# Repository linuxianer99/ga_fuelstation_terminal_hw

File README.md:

# GA_FuelStation_Terminal_HW

## Name
This is the hardware repository for GA GA_FuelStation_Terminal

## Description
KICAD Project for an RFID Terminal based on ESP32-S3

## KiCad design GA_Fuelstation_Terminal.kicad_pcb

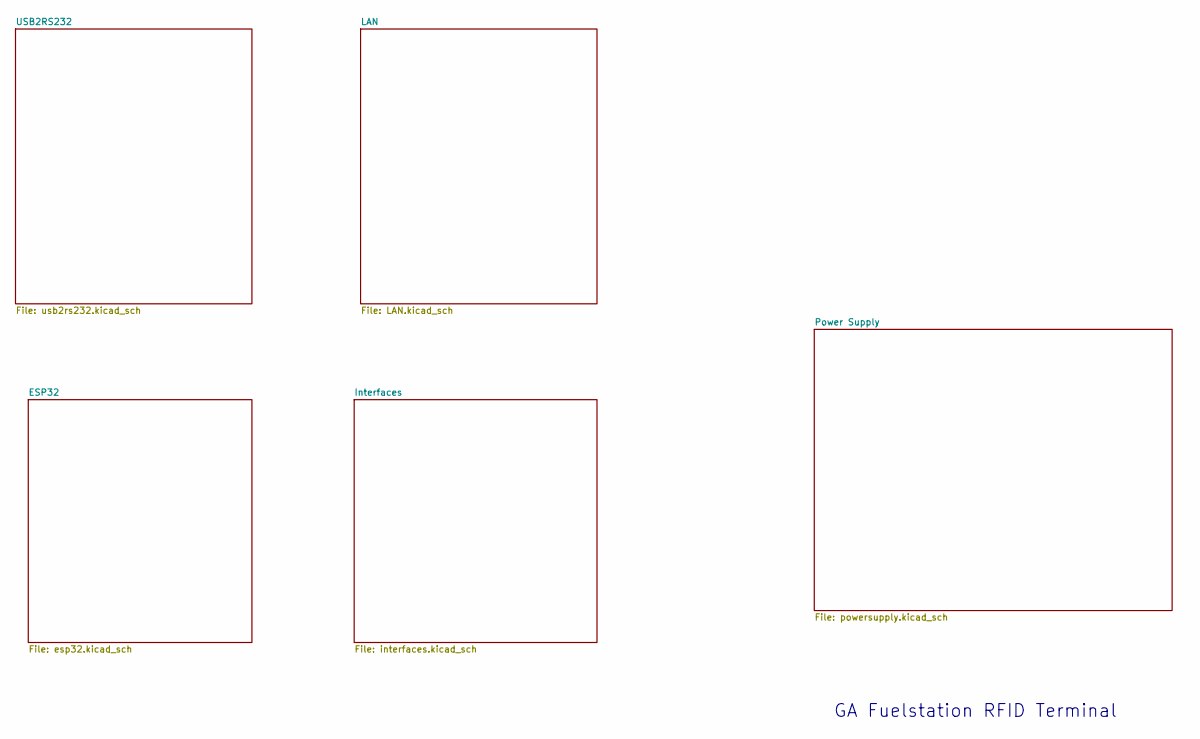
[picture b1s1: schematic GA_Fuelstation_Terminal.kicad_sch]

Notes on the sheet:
GA Fuelstation RFID Terminal

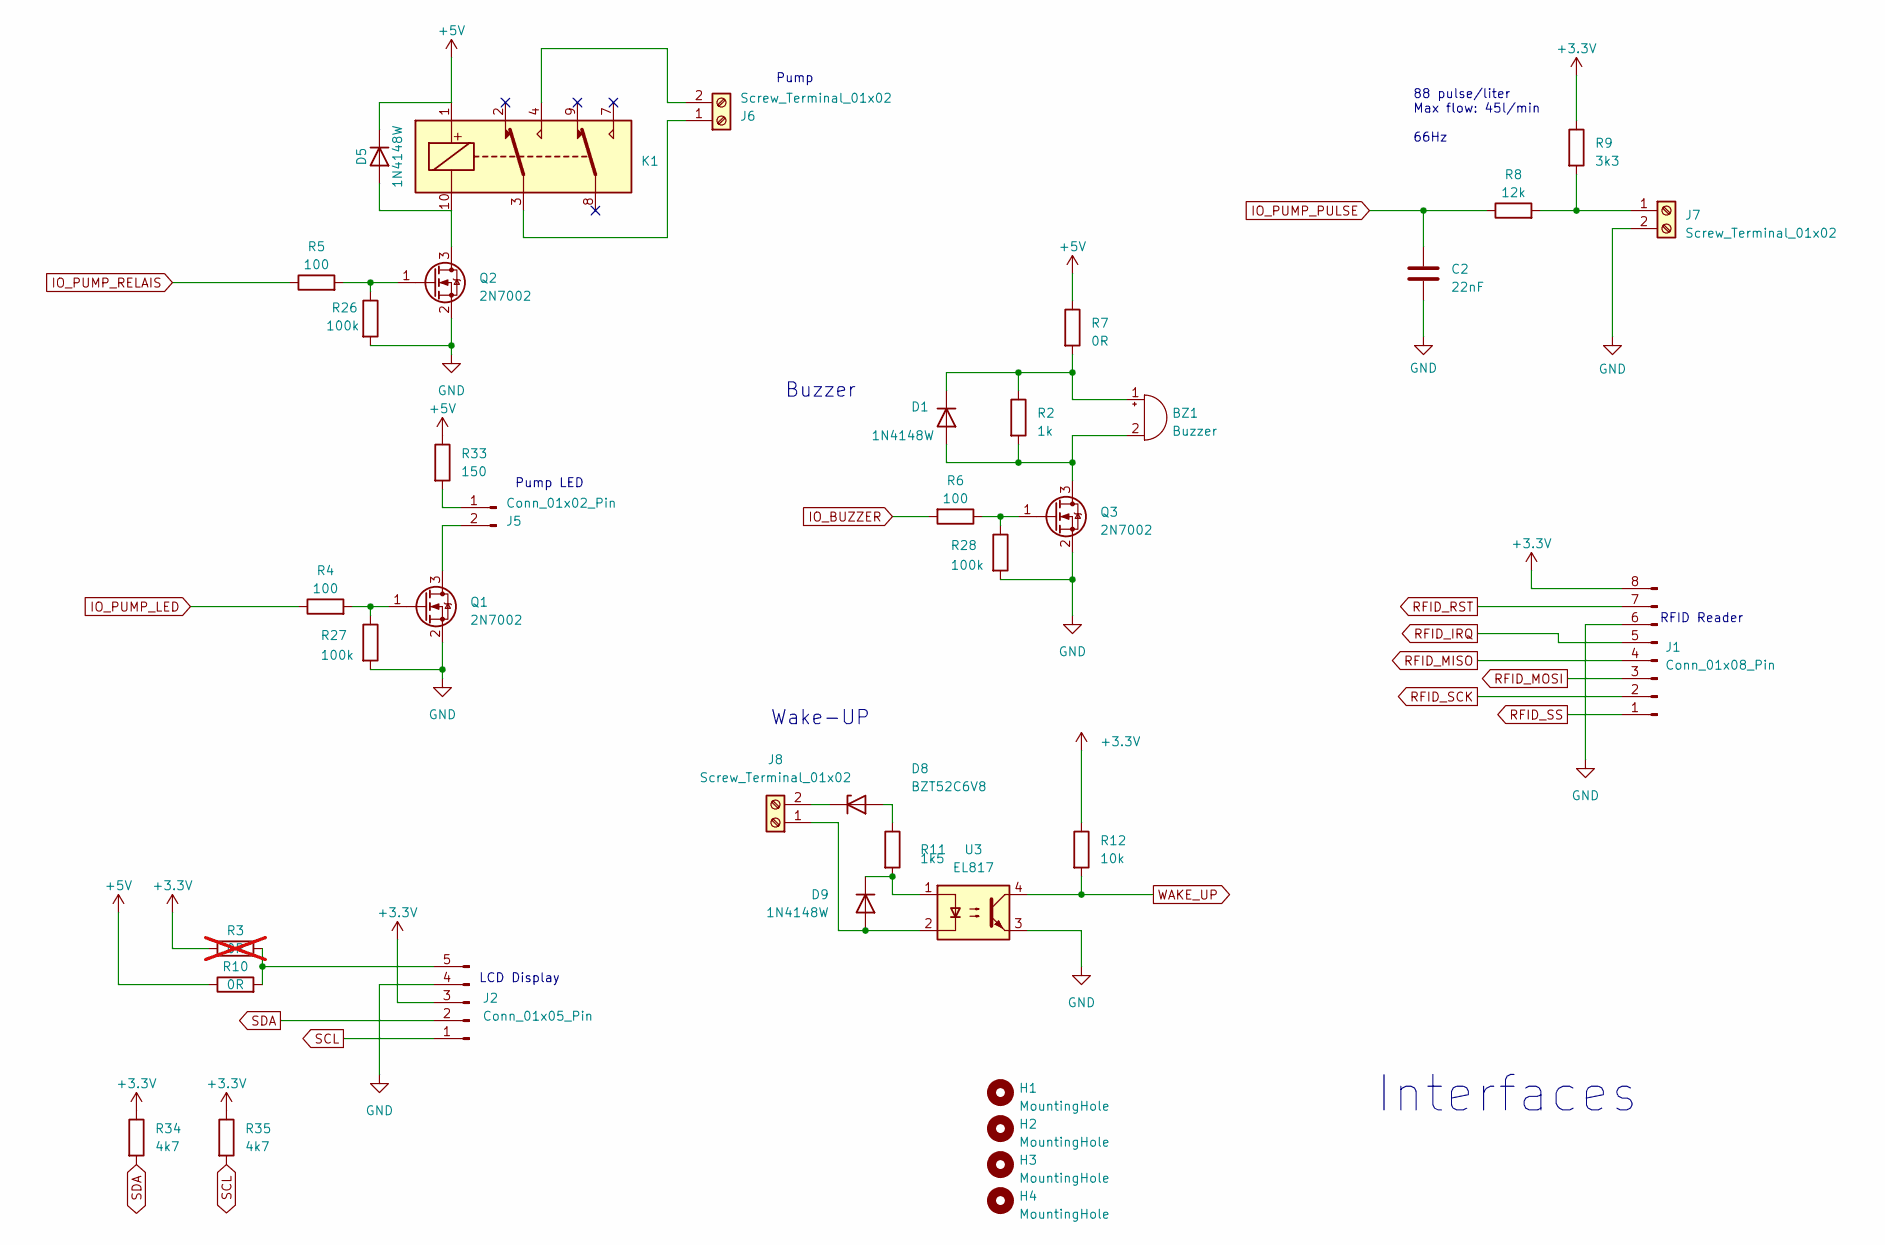
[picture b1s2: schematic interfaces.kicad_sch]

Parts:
BZ1: Buzzer; 8530-SMD; LCSC C94599
C2: 22nF; C_0603_1608Metric_Pad1.08x0.95mm_HandSolder; LCSC C21122
D1, D5, D9: 1N4148W; D_SOD-123; LCSC C81598
D8: BZT52C6V8; D_SOD-123; LCSC C173404
H1, H2, H3, H4: MountingHole; MountingHole_3.2mm_M3
J1: Conn_01x08_Pin; JST_XH_B8B-XH-AM_1x08_P2.50mm_Vertical; LCSC C161875
J2: Conn_01x05_Pin; JST_XH_B5B-XH-AM_1x05_P2.50mm_Vertical; LCSC C161872
J5: Conn_01x02_Pin; JST_XH_B2B-XH-AM_1x02_P2.50mm_Vertical; LCSC C161869
J6, J7, J8: Screw_Terminal_01x02; PhoenixContact_MSTBA_2,5_2-G-5,08_1x02_P5.08mm_Horizontal; LCSC C90074
K1: TQ2SA; LCSC C22686
Q1, Q2, Q3: 2N7002; SOT-23; LCSC C8545
R2: 1k; R_0805_2012Metric_Pad1.20x1.40mm_HandSolder; LCSC C17513
R3: 0R; R_0805_2012Metric_Pad1.20x1.40mm_HandSolder; LCSC C17477; not fitted
R4, R5, R6: 100; R_0805_2012Metric_Pad1.20x1.40mm_HandSolder; LCSC C17408
R7: 0R; R_0805_2012Metric_Pad1.20x1.40mm_HandSolder
R8: 12k; R_0805_2012Metric_Pad1.20x1.40mm_HandSolder; LCSC C17444
R9: 3k3; R_0805_2012Metric_Pad1.20x1.40mm_HandSolder; LCSC C26010
R10: 0R; R_0805_2012Metric_Pad1.20x1.40mm_HandSolder; LCSC C17477
R11: 1k5; R_0805_2012Metric_Pad1.20x1.40mm_HandSolder; LCSC C4310
R12: 10k; R_0603_1608Metric_Pad0.98x0.95mm_HandSolder; LCSC C25804
R26, R27, R28: 100k; R_0402_1005Metric_Pad0.72x0.64mm_HandSolder; LCSC C25741
R33: 150; R_0805_2012Metric_Pad1.20x1.40mm_HandSolder; LCSC C17471
R34, R35: 4k7; R_0805_2012Metric_Pad1.20x1.40mm_HandSolder; LCSC C17673
U3: EL817; SMDIP-4_W9.53mm; LCSC C63268

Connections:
+3.3V: J1.8, J2.3, R3.1, R9.1, R12.1, R34.1, R35.1; also elsewhere on the board
+5V: D5.1 (K), K1.1, R7.1, R10.1, R33.1; also elsewhere on the board
GND: C2.2, J1.6, J2.4, J7.2, Q1.2 (S), Q2.2 (S), Q3.2 (S), R26.2, R27.2, R28.2, U3.3; also elsewhere on the board
IO_BUZZER: R6.2; also elsewhere on the board
IO_PUMP_LED: R4.1; also elsewhere on the board
IO_PUMP_PULSE: C2.1, R8.1; also elsewhere on the board
IO_PUMP_RELAIS: R5.1; also elsewhere on the board
unnamed: BZ1.2 (+), D1.2 (A), Q3.3 (D), R2.2
unnamed: BZ1.1 (-), D1.1 (K), R2.1, R7.2
unnamed: D5.2 (A), K1.10, Q2.3 (D)
unnamed: D8.2 (A), R11.1
unnamed: D8.1 (K), J8.2
unnamed: D9.2 (A), J8.1, U3.2
unnamed: D9.1 (K), R11.2, U3.1
unnamed: J2.5, R3.2, R10.2
unnamed: J5.1, R33.2
unnamed: J5.2, Q1.3 (D)
unnamed: J6.1, K1.3
unnamed: J6.2, K1.4
unnamed: J7.1, R8.2, R9.2
unnamed: Q1.1 (G), R4.2, R27.1
unnamed: Q2.1 (G), R5.2, R26.1
unnamed: Q3.1 (G), R6.1, R28.1
RFID_IRQ: J1.5; also elsewhere on the board
RFID_MISO: J1.4; also elsewhere on the board
RFID_MOSI: J1.3; also elsewhere on the board
RFID_RST: J1.7; also elsewhere on the board
RFID_SCK: J1.2; also elsewhere on the board
RFID_SS: J1.1; also elsewhere on the board
SCL: J2.1, R35.2; also elsewhere on the board
SDA: J2.2, R34.2; also elsewhere on the board
WAKE_UP: R12.2, U3.4; also elsewhere on the board

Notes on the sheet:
Buzzer
RFID Reader
Pump
88 pulse/liter Max flow: 45l/min 66Hz
Wake-UP
LCD Display
Pump LED
Interfaces

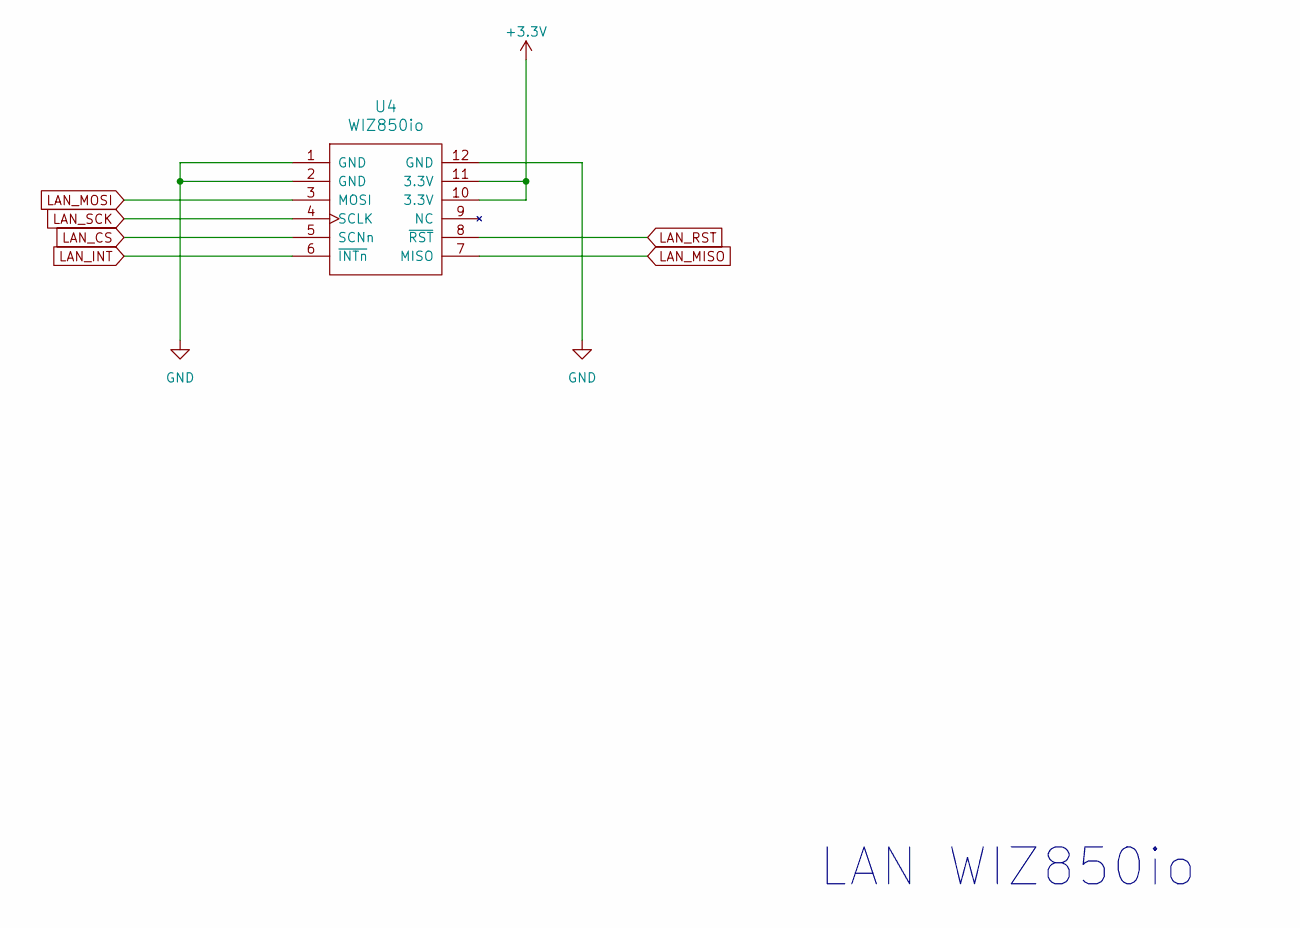
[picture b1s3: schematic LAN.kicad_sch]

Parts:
U4: WIZ850io

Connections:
+3.3V: U4.10 (3.3V), U4.11 (3.3V); also elsewhere on the board
GND: U4.1 (GND), U4.2 (GND), U4.12 (GND); also elsewhere on the board
LAN_CS: U4.5 (SCNn); also elsewhere on the board
LAN_INT: U4.6 (~INTn); also elsewhere on the board
LAN_MISO: U4.7 (MISO); also elsewhere on the board
LAN_MOSI: U4.3 (MOSI); also elsewhere on the board
LAN_RST: U4.8 (~RST); also elsewhere on the board
LAN_SCK: U4.4 (SCLK); also elsewhere on the board

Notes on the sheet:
LAN WIZ850io

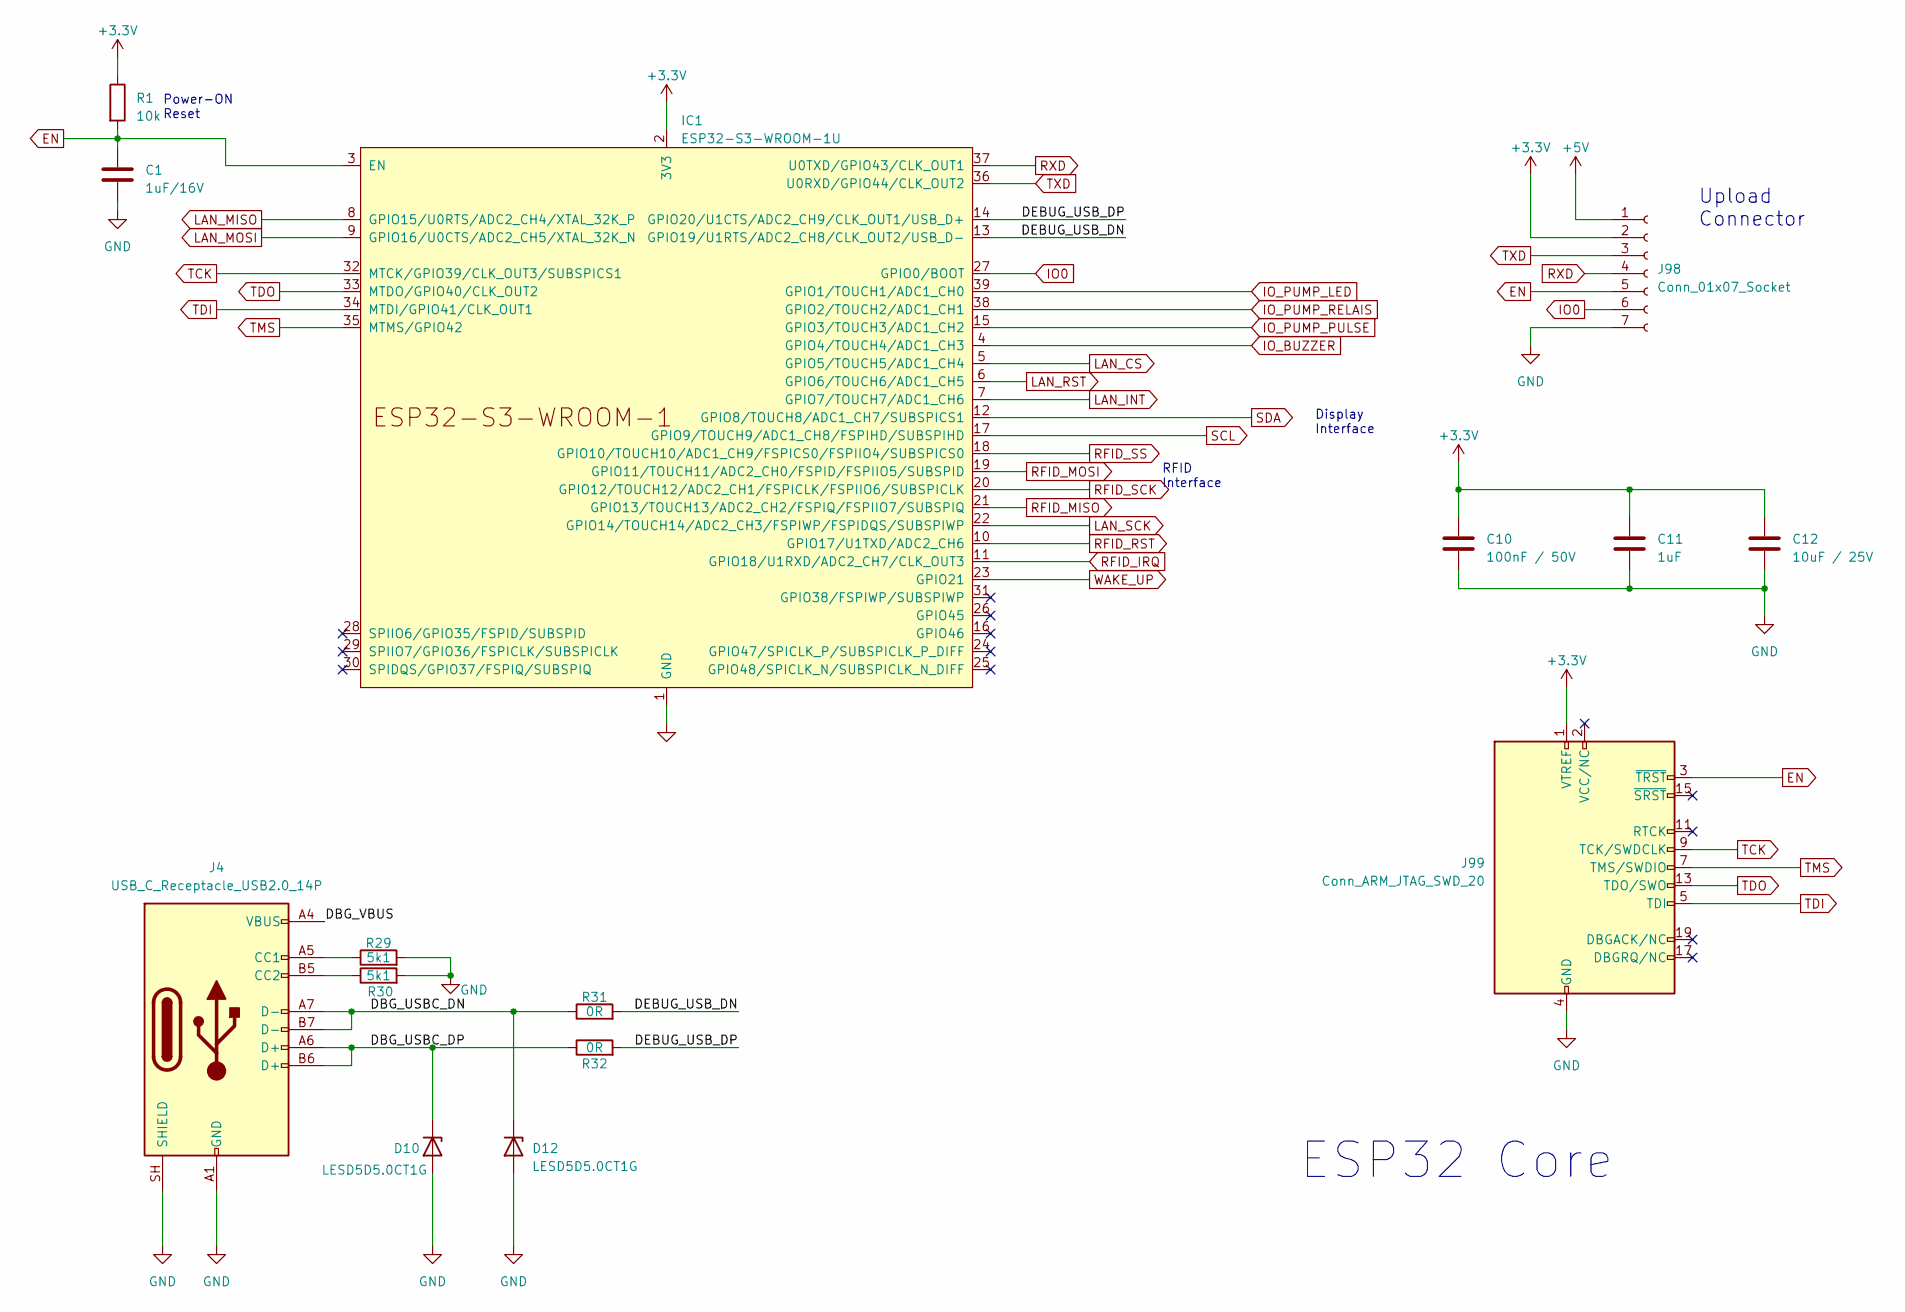
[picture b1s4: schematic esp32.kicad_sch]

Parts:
C1: 1uF/16V; C_0603_1608Metric_Pad1.08x0.95mm_HandSolder; LCSC C15849
C10: 100nF / 50V; C_0402_1005Metric_Pad0.74x0.62mm_HandSolder; LCSC C307331
C11: 1uF; C_0805_2012Metric_Pad1.18x1.45mm_HandSolder; LCSC C28323
C12: 10uF / 25V; C_1206_3216Metric_Pad1.33x1.80mm_HandSolder; LCSC C13585
D10, D12: LESD5D5.0CT1G; D_SOD-523; LCSC C41399463
IC1: ESP32-S3-WROOM-1U; LCSC C3013946
J4: USB_C_Receptacle_USB2.0_14P; USB_C_Receptacle_HRO_TYPE-C-31-M-12; LCSC C165948
J98: Conn_01x07_Socket; JST_XH_B7B-XH-AM_1x07_P2.50mm_Vertical; LCSC C161874
J99: Conn_ARM_JTAG_SWD_20; IDC-Header_2x10_P2.54mm_Vertical; LCSC C3405
R1: 10k; R_0603_1608Metric_Pad0.98x0.95mm_HandSolder; LCSC C25804
R29, R30: 5k1; R_0603_1608Metric_Pad0.98x0.95mm_HandSolder; LCSC C23186
R31, R32: 0R; R_0402_1005Metric; LCSC C17168

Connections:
+3.3V: C10.1, C11.1, C12.1, IC1.2 (3V3), J98.2, J99.1 (VTREF), R1.1; also elsewhere on the board
+5V: J98.1; also elsewhere on the board
/ESP32/DBG_USBC_DN: D12.1 (K), J4.A7 (D-), J4.B7 (D-), R31.1
/ESP32/DBG_USBC_DP: D10.1 (K), J4.A6 (D+), J4.B6 (D+), R32.1
/ESP32/DBG_VBUS: J4.A4 (VBUS), J4.A9 (VBUS), J4.B4 (VBUS), J4.B9 (VBUS)
/ESP32/DEBUG_USB_DN: IC1.13 (GPIO19/U1RTS/ADC2_CH8/CLK_OUT2/USB_D-), R31.2
/ESP32/DEBUG_USB_DP: IC1.14 (GPIO20/U1CTS/ADC2_CH9/CLK_OUT1/USB_D+), R32.2
EN: C1.1, IC1.3 (EN), J98.5, J99.3 (~TRST), R1.2; also elsewhere on the board
GND: C1.2, C10.2, C11.2, C12.2, D10.2 (A), D12.2 (A), IC1.1 (GND), IC1.40 (GND), IC1.41 (GND), J4.A1 (GND), J4.A12 (GND), J4.B1 (GND), J4.B12 (GND), J4.SH (SHIELD), J98.7, J99.4 (GND), J99.6 (GND), J99.8 (GND), J99.10 (GND), J99.12 (GND), J99.14 (GND), J99.16 (GND), J99.18 (GND), J99.20 (GND), R29.2, R30.2; also elsewhere on the board
IO0: IC1.27 (GPIO0/BOOT), J98.6; also elsewhere on the board
IO_BUZZER: IC1.4 (GPIO4/TOUCH4/ADC1_CH3); also elsewhere on the board
IO_PUMP_LED: IC1.39 (GPIO1/TOUCH1/ADC1_CH0); also elsewhere on the board
IO_PUMP_PULSE: IC1.15 (GPIO3/TOUCH3/ADC1_CH2); also elsewhere on the board
IO_PUMP_RELAIS: IC1.38 (GPIO2/TOUCH2/ADC1_CH1); also elsewhere on the board
LAN_CS: IC1.5 (GPIO5/TOUCH5/ADC1_CH4); also elsewhere on the board
LAN_INT: IC1.7 (GPIO7/TOUCH7/ADC1_CH6); also elsewhere on the board
LAN_MISO: IC1.8 (GPIO15/U0RTS/ADC2_CH4/XTAL_32K_P); also elsewhere on the board
LAN_MOSI: IC1.9 (GPIO16/U0CTS/ADC2_CH5/XTAL_32K_N); also elsewhere on the board
LAN_RST: IC1.6 (GPIO6/TOUCH6/ADC1_CH5); also elsewhere on the board
LAN_SCK: IC1.22 (GPIO14/TOUCH14/ADC2_CH3/FSPIWP/FSPIDQS/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); also elsewhere on the board
unnamed: J4.A5 (CC1), R29.1
unnamed: J4.B5 (CC2), R30.1
RFID_IRQ: IC1.11 (GPIO18/U1RXD/ADC2_CH7/CLK_OUT3); also elsewhere on the board
RFID_MISO: IC1.21 (GPIO13/TOUCH13/ADC2_CH2/FSPIQ/FSPIIO7/S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); also elsewhere on the board
RFID_MOSI: IC1.19 (GPIO11/TOUCH11/ADC2_CH0/FSPID/FSPIIO5/S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); also elsewhere on the board
RFID_RST: IC1.10 (GPIO17/U1TXD/ADC2_CH6); also elsewhere on the board
RFID_SCK: IC1.20 (GPIO12/TOUCH12/ADC2_CH1/FSPICLK/FSPIIO6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); also elsewhere on the board
RFID_SS: IC1.18 (GPIO10/TOUCH10/ADC1_CH9/FSPICS0/FSPIIO4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); also elsewhere on the board
RXD: IC1.37 (U0TXD/GPIO43/CLK_OUT1), J98.4; also elsewhere on the board
SCL: IC1.17 (GPIO9/TOUCH9/ADC1_CH8/FSPIHD/SUBSPIHD); also elsewhere on the board
SDA: IC1.12 (GPIO8/TOUCH8/ADC1_CH7/SUBSPICS1); also elsewhere on the board
TCK: IC1.32 (MTCK/GPIO39/CLK_OUT3/SUBSPICS1), J99.9 (TCK/SWDCLK)
TDI: IC1.34 (MTDI/GPIO41/CLK_OUT1), J99.5 (TDI)
TDO: IC1.33 (MTDO/GPIO40/CLK_OUT2), J99.13 (TDO/SWO)
TMS: IC1.35 (MTMS/GPIO42), J99.7 (TMS/SWDIO)
TXD: IC1.36 (U0RXD/GPIO44/CLK_OUT2), J98.3; also elsewhere on the board
WAKE_UP: IC1.23 (GPIO21); also elsewhere on the board

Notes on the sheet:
Upload Connector
ESP32 Core
Display Interface
RFID Interface
Power-ON Reset

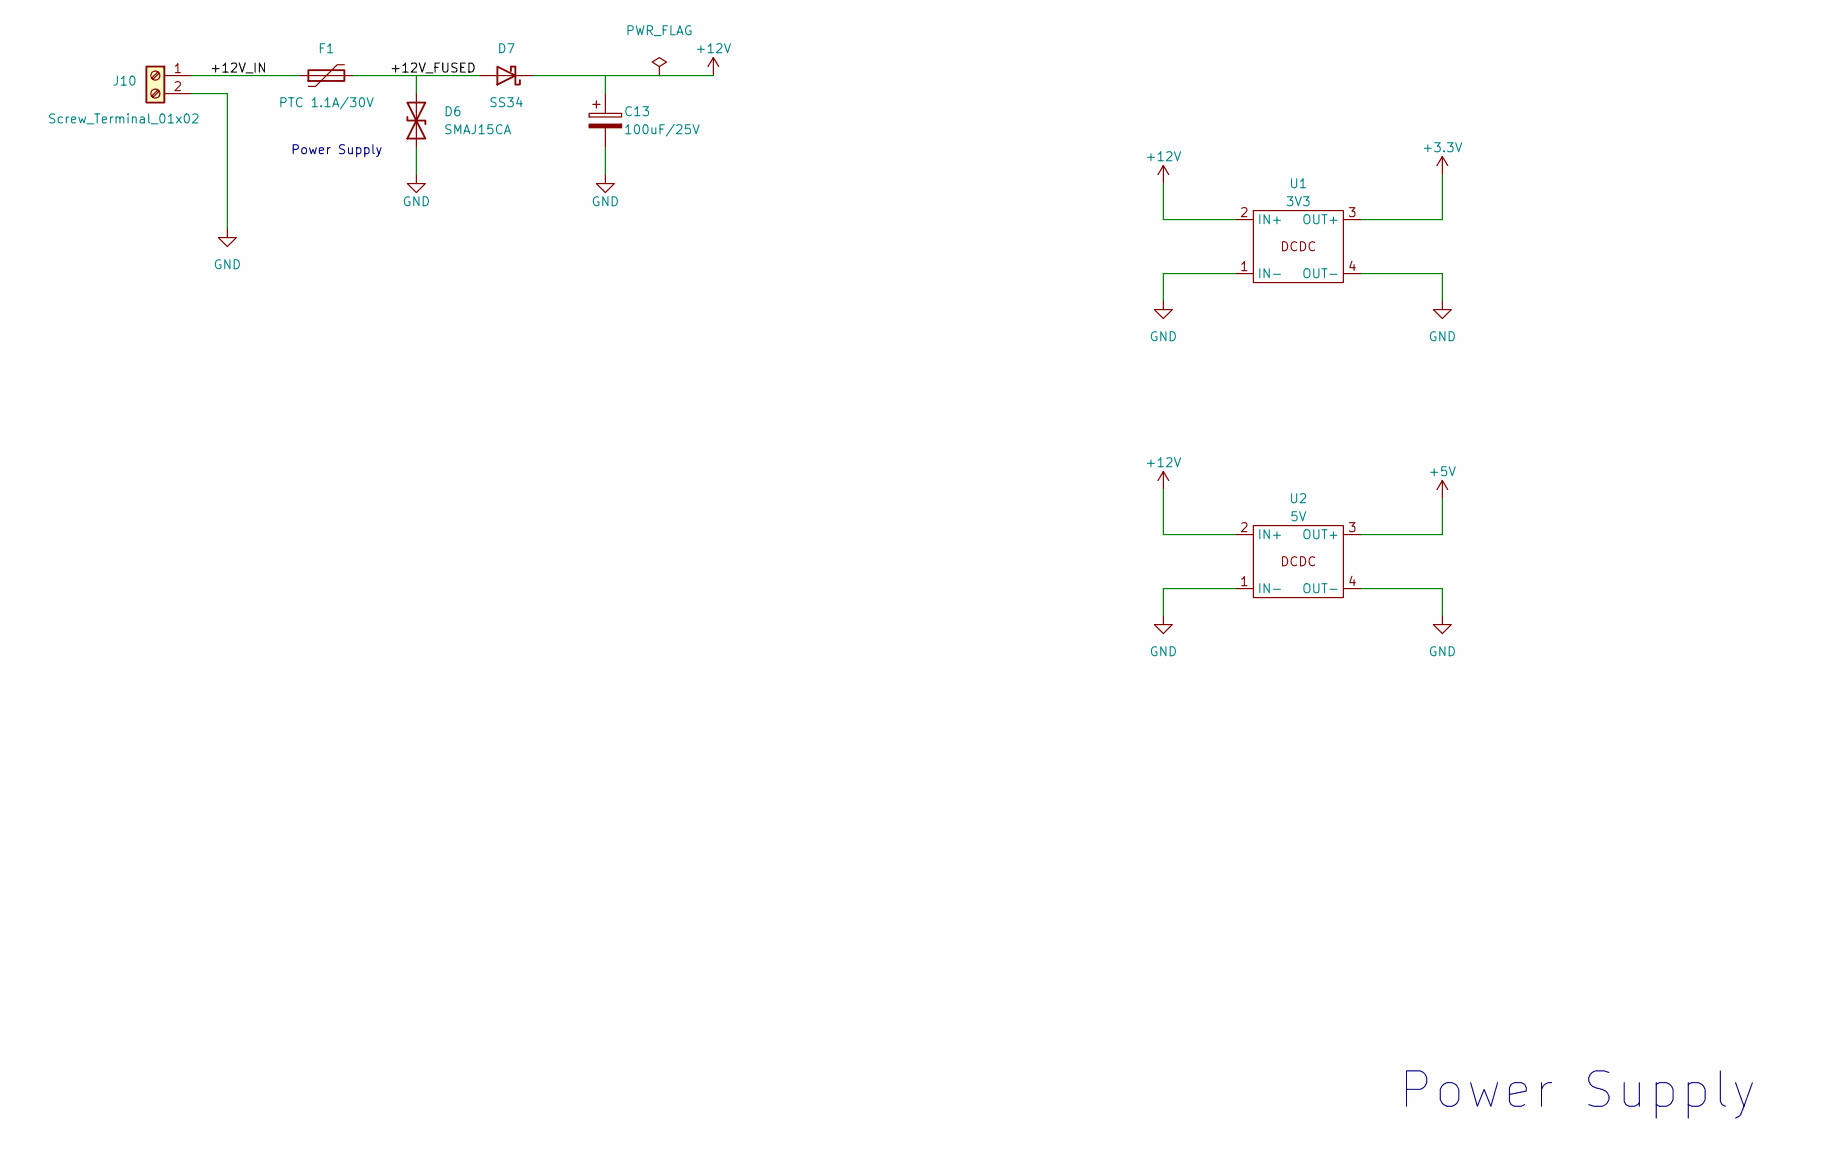
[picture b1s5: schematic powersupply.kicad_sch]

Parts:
C13: 100uF/25V; CP_Elec_6.3x7.7; LCSC C72477
D6: SMAJ15CA; D_SMA; LCSC C151939
D7: SS34; D_SMA; LCSC C8678
F1: PTC 1.1A/30V; Fuse_1812_4532Metric; LCSC C70119
J10: Screw_Terminal_01x02; PhoenixContact_MSTBA_2,5_2-G-5,08_1x02_P5.08mm_Horizontal; LCSC C90074
U1: 3V3; XLZMYQ
U2: 5V; XLZMYQ

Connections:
+3.3V: U1.3 (OUT+); also elsewhere on the board
+5V: U2.3 (OUT+); also elsewhere on the board
+12V: C13.1, D7.1 (K), U1.2 (IN+), U2.2 (IN+)
/Power Supply/+12V_FUSED: D6.2 (A2), D7.2 (A), F1.2
/Power Supply/+12V_IN: F1.1, J10.1
GND: C13.2, D6.1 (A1), J10.2, U1.1 (IN-), U1.4 (OUT-), U2.1 (IN-), U2.4 (OUT-); also elsewhere on the board

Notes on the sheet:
Power Supply

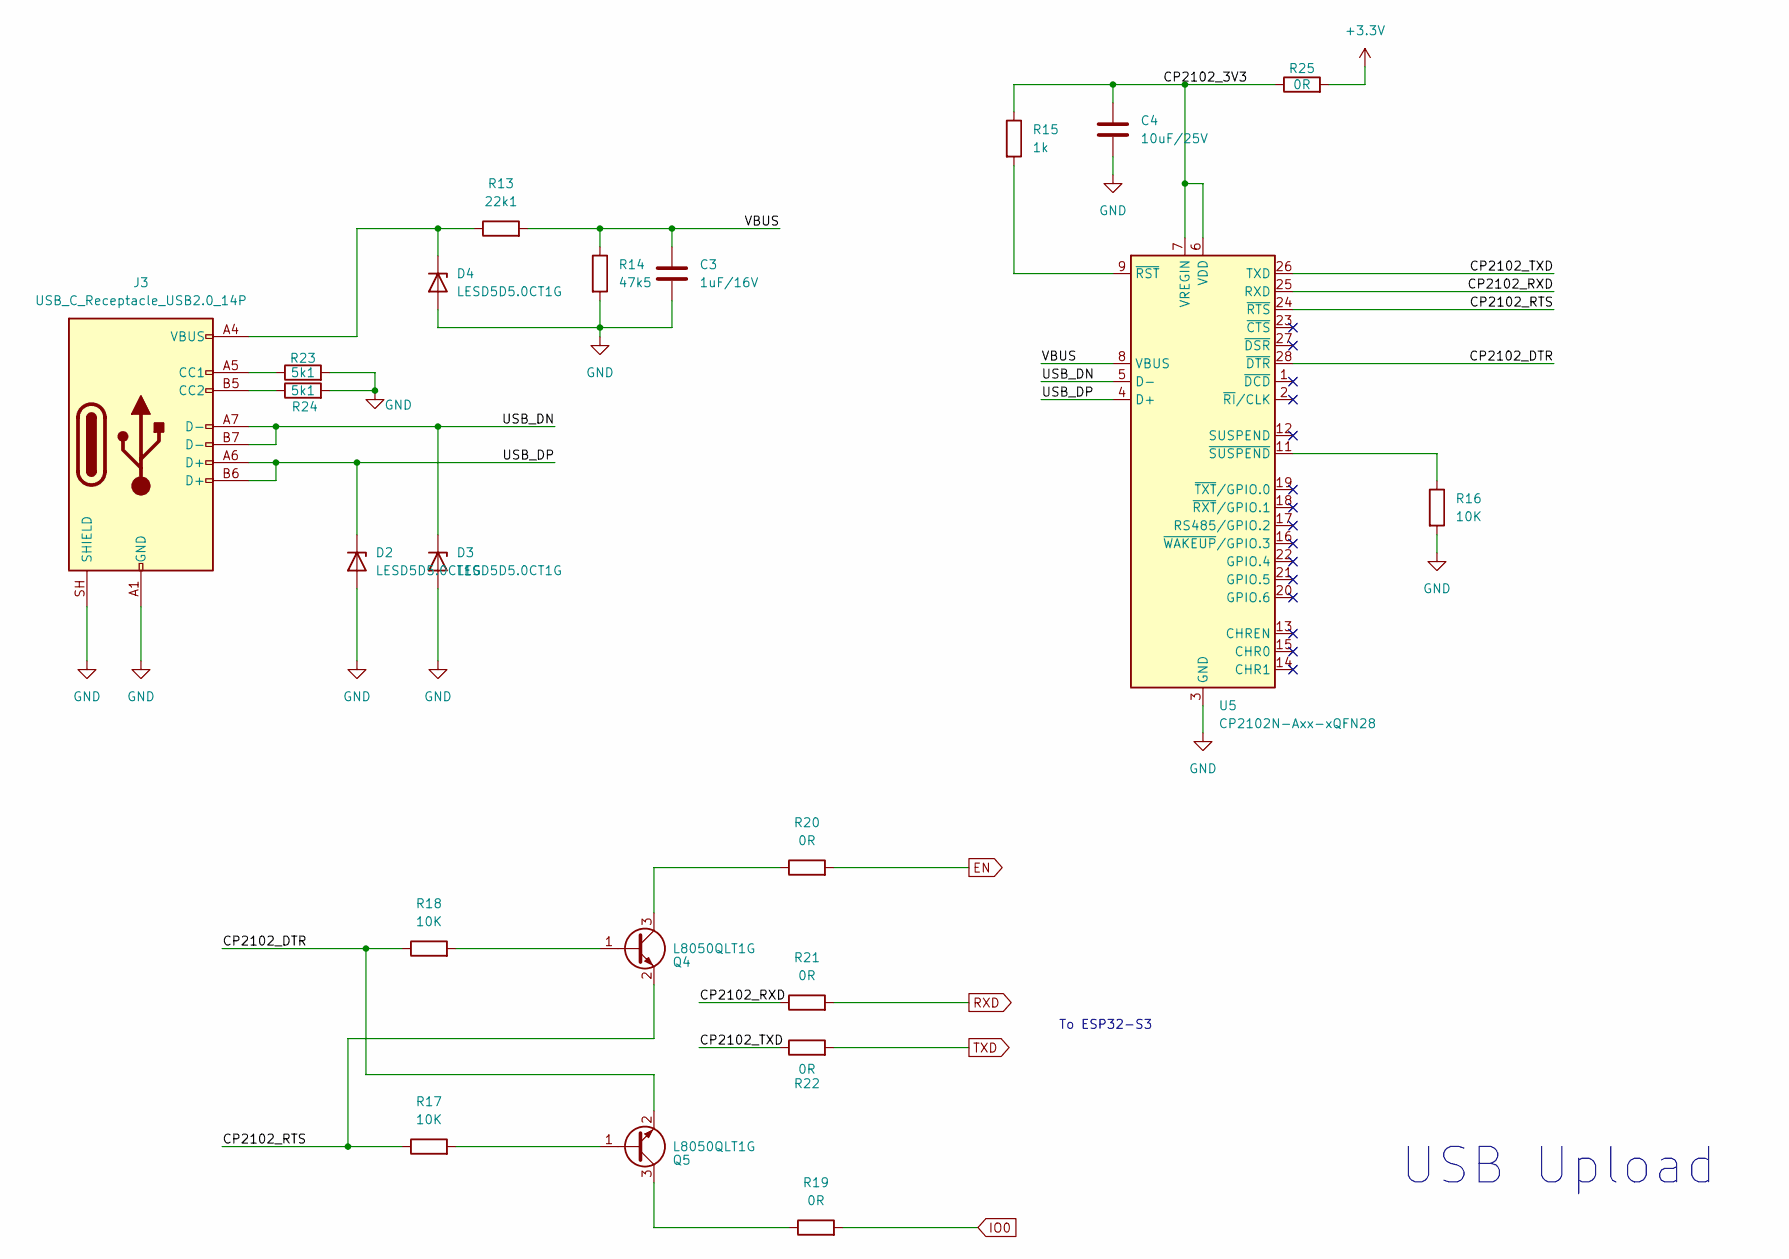
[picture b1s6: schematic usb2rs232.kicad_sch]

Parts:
C3: 1uF/16V; C_0603_1608Metric; LCSC C15849
C4: 10uF/25V; C_0603_1608Metric; LCSC C96446
D2, D3, D4: LESD5D5.0CT1G; D_SOD-523; LCSC C41399463
J3: USB_C_Receptacle_USB2.0_14P; USB_C_Receptacle_HRO_TYPE-C-31-M-12; LCSC C165948
Q4, Q5: L8050QLT1G; SOT-23; LCSC C49581
R13: 22k1; R_0402_1005Metric; LCSC C163478
R14: 47k5; R_0402_1005Metric; LCSC C324818
R15: 1k; R_0402_1005Metric; LCSC C11702
R16, R17, R18: 10K; R_0402_1005Metric; LCSC C25744
R19, R20, R21, R22: 0R; R_0402_1005Metric; LCSC C17168
R23, R24: 5k1; R_0603_1608Metric_Pad0.98x0.95mm_HandSolder; LCSC C23186
R25: 0R; R_0402_1005Metric_Pad0.72x0.64mm_HandSolder; LCSC C17168
U5: CP2102N-Axx-xQFN28; QFN-28-1EP_5x5mm_P0.5mm_EP3.35x3.35mm; LCSC C964632

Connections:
+3.3V: R25.2; also elsewhere on the board
/USB2RS232/CP2102_3V3: C4.1, R15.1, R25.1, U5.6 (VDD), U5.7 (VREGIN)
/USB2RS232/CP2102_DTR: Q5.2 (E), R18.1, U5.28 (~DTR)
/USB2RS232/CP2102_RTS: Q4.2 (E), R17.1, U5.24 (~RTS)
/USB2RS232/CP2102_RXD: R21.1, U5.25 (RXD)
/USB2RS232/CP2102_TXD: R22.1, U5.26 (TXD)
/USB2RS232/USB_DN: D3.1 (K), J3.A7 (D-), J3.B7 (D-), U5.5 (D-)
/USB2RS232/USB_DP: D2.1 (K), J3.A6 (D+), J3.B6 (D+), U5.4 (D+)
/USB2RS232/VBUS: C3.1, R13.2, R14.1, U5.8 (VBUS)
EN: R20.2; also elsewhere on the board
GND: C3.2, C4.2, D2.2 (A), D3.2 (A), D4.2 (A), J3.A1 (GND), J3.A12 (GND), J3.B1 (GND), J3.B12 (GND), J3.SH (SHIELD), R14.2, R16.2, R23.2, R24.2, U5.3 (GND), U5.29 (GND); also elsewhere on the board
IO0: R19.2; also elsewhere on the board
unnamed: D4.1 (K), J3.A4 (VBUS), J3.A9 (VBUS), J3.B4 (VBUS), J3.B9 (VBUS), R13.1
unnamed: J3.A5 (CC1), R23.1
unnamed: J3.B5 (CC2), R24.1
unnamed: Q4.1 (B), R18.2
unnamed: Q4.3 (C), R20.1
unnamed: Q5.1 (B), R17.2
unnamed: Q5.3 (C), R19.1
unnamed: R15.2, U5.9 (~RST)
unnamed: R16.1, U5.11 (~SUSPEND)
RXD: R21.2; also elsewhere on the board
TXD: R22.2; also elsewhere on the board

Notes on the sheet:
To ESP32-S3
USB Upload

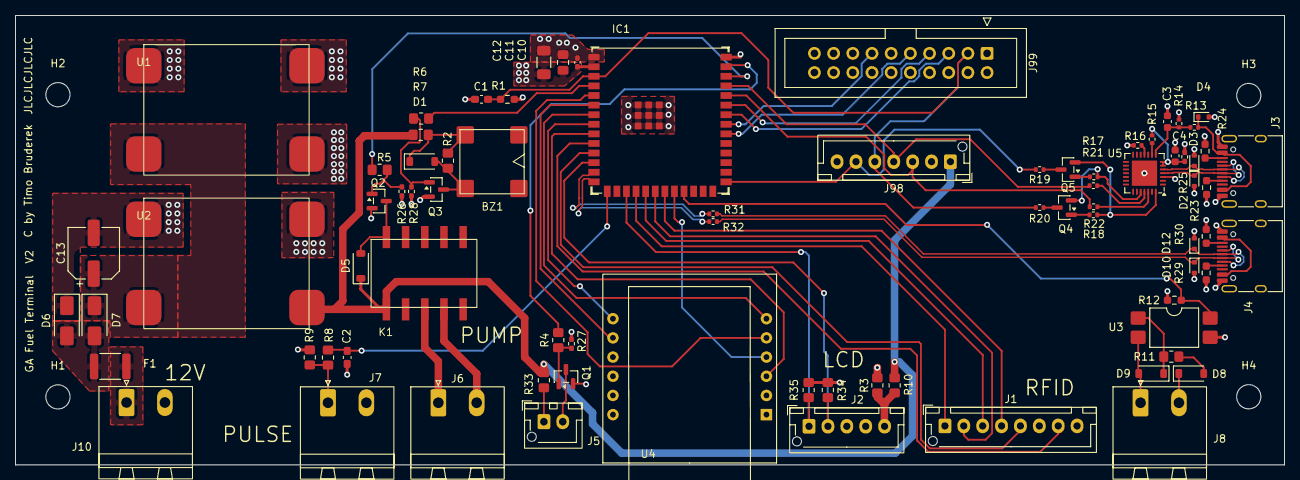
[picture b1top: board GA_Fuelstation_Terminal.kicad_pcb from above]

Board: 4 copper layers, 168.0 x 59.5 mm, 83 parts (0 on the bottom side), 73 nets.

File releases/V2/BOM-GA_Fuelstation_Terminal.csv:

Comment,Designator,Footprint,LCSC,Quantity
0R,"R19,R20,R21,R22,R25,R31,R32",R_0402_1005Metric,C17168,7
0R,R10,R_0805_2012Metric_Pad1.20x1.40mm_HandSolder,C17477,1
100,"R4,R5,R6",R_0805_2012Metric_Pad1.20x1.40mm_HandSolder,C17408,3
100k,"R26,R27,R28",R_0402_1005Metric_Pad0.72x0.64mm_HandSolder,C25741,3
100nF / 50V,C10,C_0402_1005Metric_Pad0.74x0.62mm_HandSolder,C307331,1
100uF/25V,C13,CP_Elec_6.3x7.7,C696783,1
10K,"R16,R17,R18",R_0402_1005Metric,C25744,3
10k,"R1,R12",R_0603_1608Metric_Pad0.98x0.95mm_HandSolder,C25804,2
10uF / 25V,C12,C_1206_3216Metric_Pad1.33x1.80mm_HandSolder,C13585,1
10uF/25V,C4,C_0603_1608Metric,C96446,1
12k,R8,R_0805_2012Metric_Pad1.20x1.40mm_HandSolder,C17444,1
150,R33,R_0805_2012Metric_Pad1.20x1.40mm_HandSolder,C17471,1
1N4148W,"D1,D5,D9",D_SOD-123,C81598,3
1k,R15,R_0402_1005Metric,C11702,1
1k,R2,R_0805_2012Metric_Pad1.20x1.40mm_HandSolder,C17513,1
1k5,R11,R_0805_2012Metric_Pad1.20x1.40mm_HandSolder,C4310,1
1uF,C11,C_0805_2012Metric_Pad1.18x1.45mm_HandSolder,C28323,1
1uF/16V,"C1,C3",C_0603_1608Metric_Pad1.08x0.95mm_HandSolder,C15849,2
22k1,R13,R_0402_1005Metric,C163478,1
22nF,C2,C_0603_1608Metric_Pad1.08x0.95mm_HandSolder,C21122,1
2N7002,"Q1,Q2,Q3",SOT-23,C8545,3
3k3,R9,R_0805_2012Metric_Pad1.20x1.40mm_HandSolder,C26010,1
47k5,R14,R_0402_1005Metric,C324818,1
4k7,"R34,R35",R_0805_2012Metric_Pad1.20x1.40mm_HandSolder,C17673,2
5k1,"R23,R24,R29,R30",R_0603_1608Metric_Pad0.98x0.95mm_HandSolder,C23186,4
BZT52C6V8,D8,D_SOD-123,C173404,1
Buzzer,BZ1,8530-SMD,C94599,1
CP2102N-Axx-xQFN28,U5,QFN-28-1EP_5x5mm_P0.5mm_EP3.35x3.35mm,C964632,1
Conn_01x02_Pin,J5,JST_XH_B2B-XH-AM_1x02_P2.50mm_Vertical,C161869,1
Conn_01x05_Pin,J2,JST_XH_B5B-XH-AM_1x05_P2.50mm_Vertical,C2318,1
Conn_01x07_Socket,J98,JST_XH_B7B-XH-AM_1x07_P2.50mm_Vertical,C161874,1
Conn_01x08_Pin,J1,JST_XH_B8B-XH-AM_1x08_P2.50mm_Vertical,C10385,1
Conn_ARM_JTAG_SWD_20,J99,IDC-Header_2x10_P2.54mm_Vertical,C3405,1
EL817,U3,SMDIP-4_W9.53mm,C63268,1
ESP32-S3-WROOM-1U,IC1,ESP32-S3-WROOM-1U,C3013946,1
L8050QLT1G,"Q4,Q5",SOT-23,C49581,2
LESD5D5.0CT1G,"D10,D12,D2,D3,D4",D_SOD-523,C41399463,5
PTC 1.1A/30V,F1,Fuse_1812_4532Metric,C70119,1
SMAJ15CA,D6,D_SMA,C151939,1
SS34,D7,D_SMA,C8678,1
Screw_Terminal_01x02,"J10,J6,J7,J8","PhoenixContact_MSTBA_2,5_2-G-5,08_1x02_P5.08mm_Horizontal",C90074,4
USB_C_Receptacle_USB2.0_14P,"J3,J4",USB_C_Receptacle_HRO_TYPE-C-31-M-12,C165948,2
~,K1,TQ2SA,C22686,1
0R,R7,R_0805_2012Metric_Pad1.20x1.40mm_HandSolder,,1

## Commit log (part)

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2023-06-21 Add 3D pics of PCB
2023-06-21 Add gitignore
2023-06-21 Cleanup production files
2023-06-21 Release V1
2023-06-21 Add schematic PDF
